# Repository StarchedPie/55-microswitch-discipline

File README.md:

# 55%
 55% keyboard using D2F microswitches, based on Coseyfannitutti's Discipline

[BOM, Build Guide, and Flashing Information](./doc)

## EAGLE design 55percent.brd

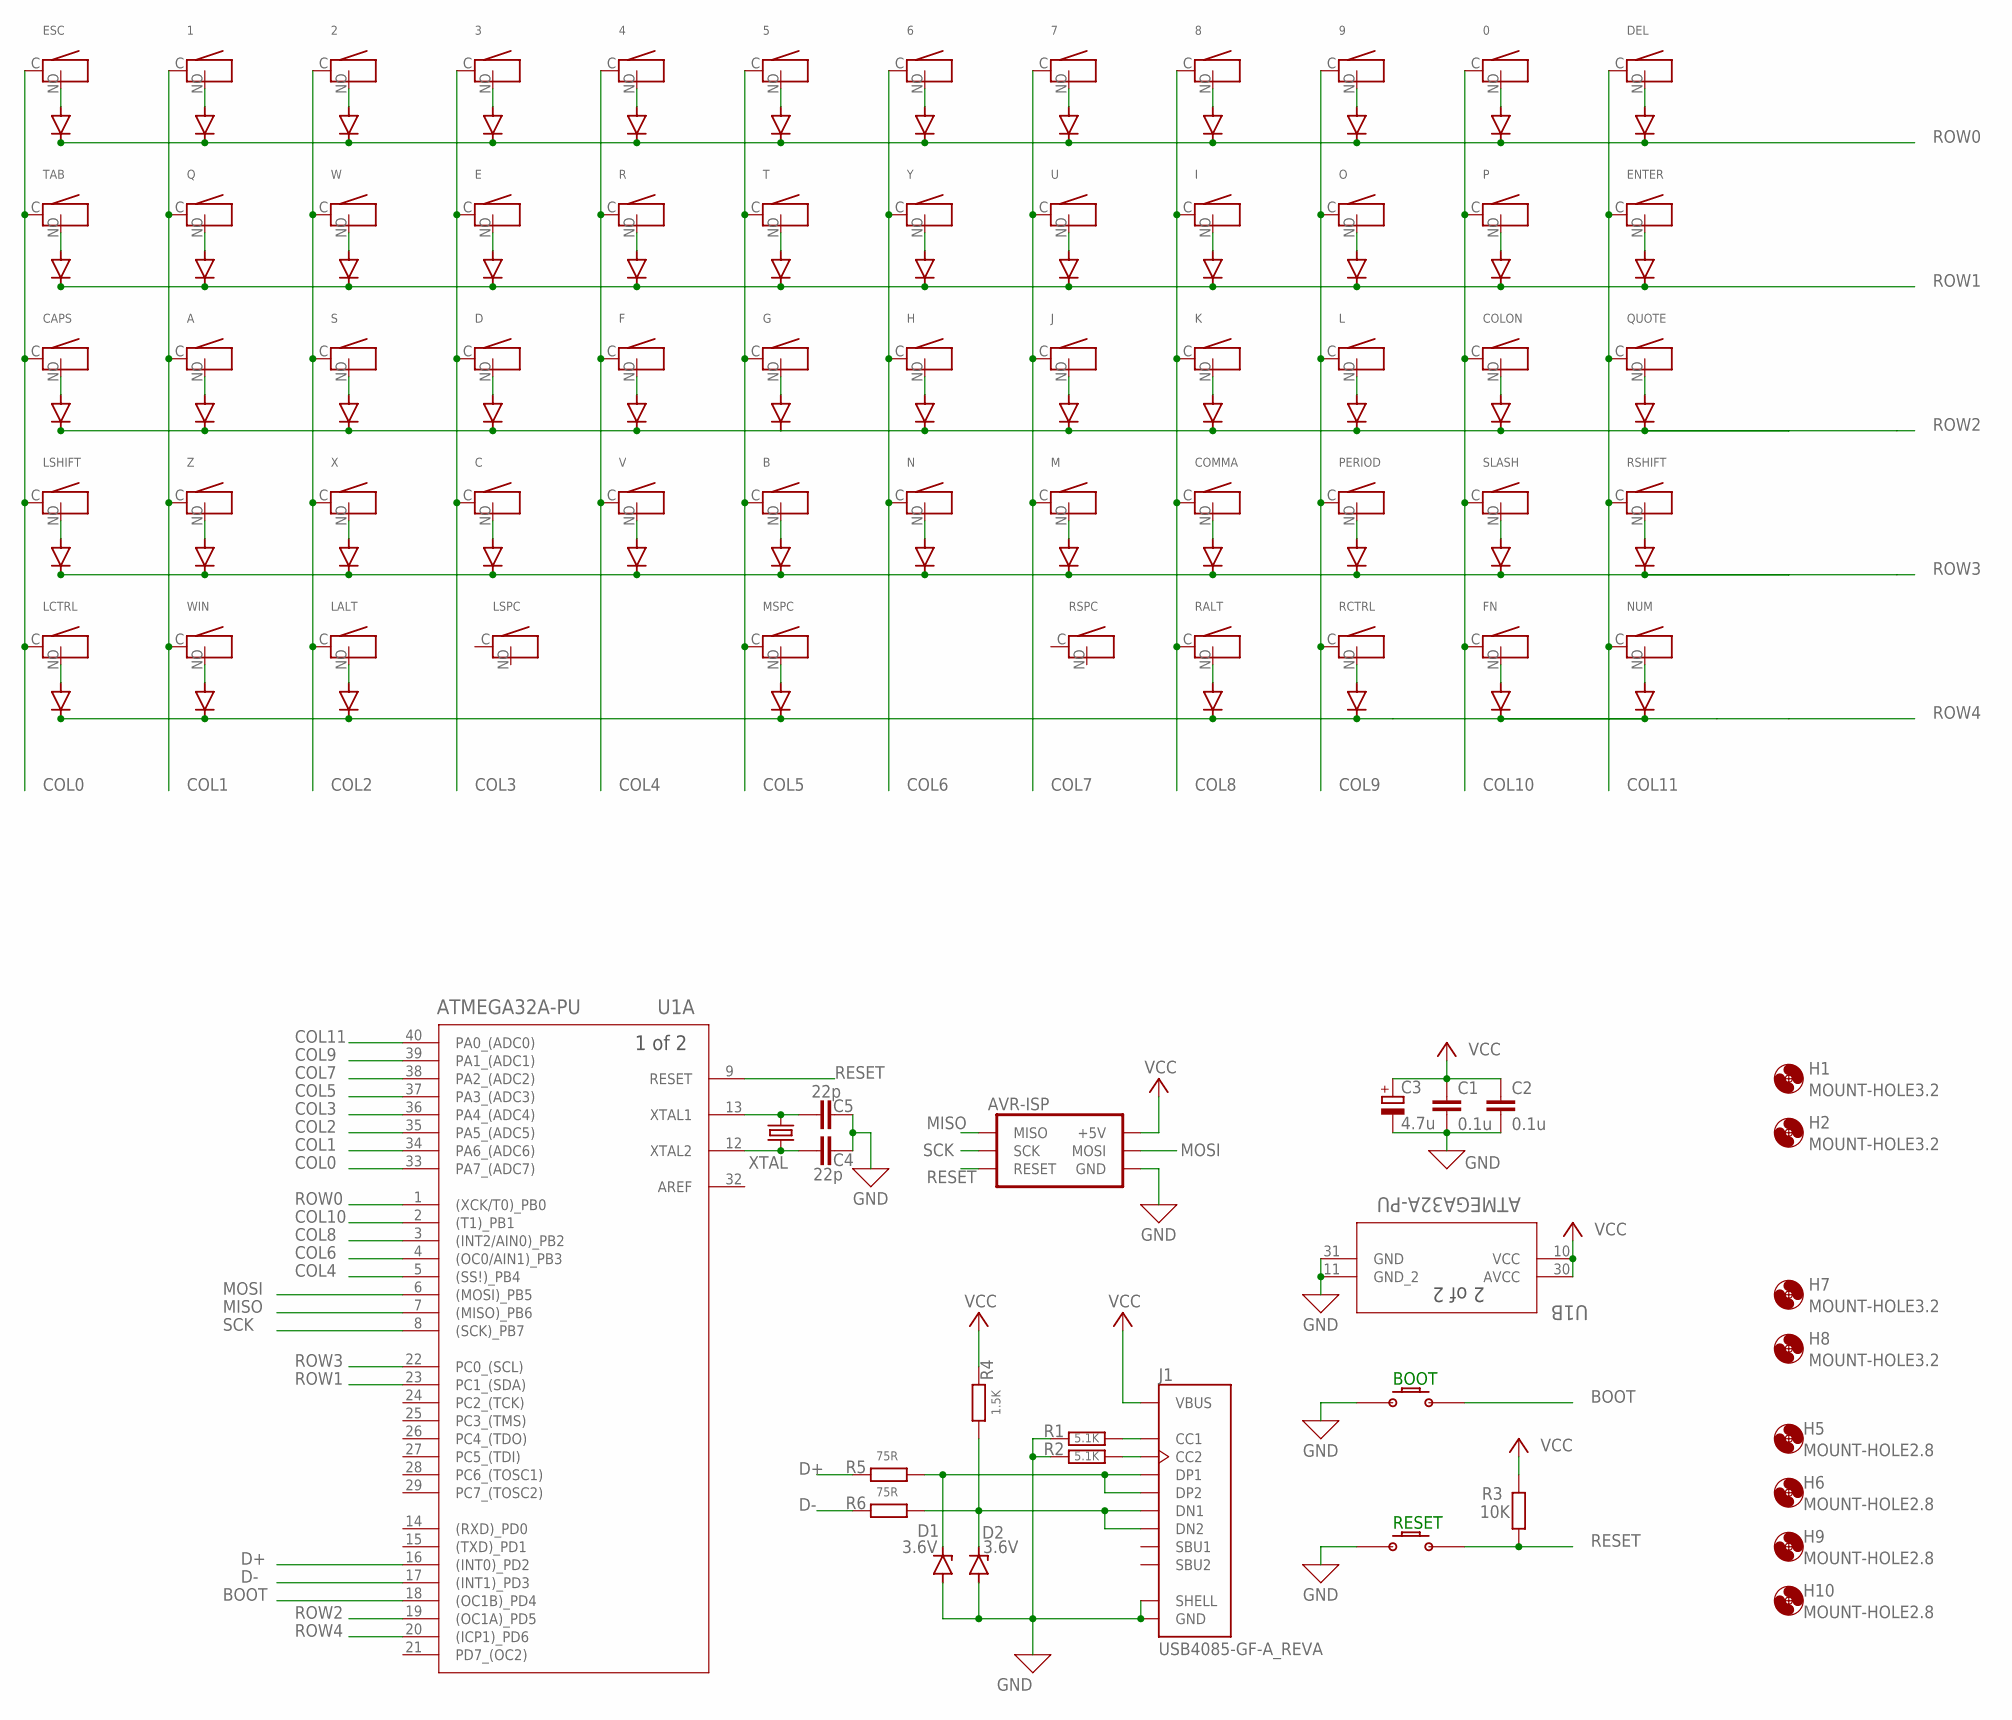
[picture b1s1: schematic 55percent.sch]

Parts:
0, 1, 2, 3, 4, 5, 6, 7, 8, 9: D2F_MICROSWITCH
A: D2F_MICROSWITCH
B: D2F_MICROSWITCH
C: D2F_MICROSWITCH
C1, C2: 0.1u; C025-024X044
C3: 4.7u; E2,5-5
C4, C5: 22p; C025-024X044
CAPS: D2F_MICROSWITCH
COLON: D2F_MICROSWITCH
COMMA: D2F_MICROSWITCH
D: D2F_MICROSWITCH
D1, D2: 3.6V; DO34Z7
D3, D4, D5, D6, D7, D8, D9, D10, D11, D12, D13, D14, D15, D16, D17, D18, D19, D20, D21, D23, D24, D25, D26, D28, D29, D30, D31, D32, D33, D34, D35, D36, D38, D39, D40, D41, D43, D44, D45, D46, D47, D48, D49, D50, D51, D52, D53, D54, D55, D56, D57, D58, D59, D60, D61, D62: 1N4004; DO41-10
DEL: D2F_MICROSWITCH
E: D2F_MICROSWITCH
ENTER: D2F_MICROSWITCH
ESC: D2F_MICROSWITCH
F: D2F_MICROSWITCH
FN: D2F_MICROSWITCH
G: D2F_MICROSWITCH
H: D2F_MICROSWITCH
H1, H2, H7, H8: MOUNT-HOLE3.2; 3,2
H5, H6, H9, H10: MOUNT-HOLE2.8; 2,2
I: D2F_MICROSWITCH
J: D2F_MICROSWITCH
J1: USB4085-GF-A_REVA; GCT_USB4085-GF-A_REVA
JP1: PINHD-2X3; 2X03
K: D2F_MICROSWITCH
L: D2F_MICROSWITCH
LALT: D2F_MICROSWITCH
LCTRL: D2F_MICROSWITCH
LSHIFT: D2F_MICROSWITCH
LSPC: D2F_MICROSWITCH
M: D2F_MICROSWITCH
MSPC: D2F_MICROSWITCH
N: D2F_MICROSWITCH
NUM: D2F_MICROSWITCH
O: D2F_MICROSWITCH
P: D2F_MICROSWITCH
PERIOD: D2F_MICROSWITCH
Q: D2F_MICROSWITCH
QUOTE: D2F_MICROSWITCH
R: D2F_MICROSWITCH
R1, R2: 5.1K; 0207/10
R3: 10K; 0207/10
R4: 1.5K; 0207/10
R5, R6: 75R; 0207/10
RALT: D2F_MICROSWITCH
RCTRL: D2F_MICROSWITCH
RSHIFT: D2F_MICROSWITCH
RSPC: D2F_MICROSWITCH
S: D2F_MICROSWITCH
SLASH: D2F_MICROSWITCH
T: D2F_MICROSWITCH
TAB: D2F_MICROSWITCH
U: D2F_MICROSWITCH
U1: ATMEGA32A-PU; 40P6
U$1, U$2: PTS636SK43LFS; PTS636SK43LFSTHT
V: D2F_MICROSWITCH
W: D2F_MICROSWITCH
WIN: D2F_MICROSWITCH
X: D2F_MICROSWITCH
XTAL: CRYSTALHC49S; HC49/S
Y: D2F_MICROSWITCH
Z: D2F_MICROSWITCH

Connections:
BOOT: U1.18 ((OC1B)_PD4), U$1.P$2
COL0: CAPS.C, ESC.C, LCTRL.C, LSHIFT.C, TAB.C, U1.33 (PA7_(ADC7))
COL1: 1.C, A.C, Q.C, U1.34 (PA6_(ADC6)), WIN.C, Z.C
COL2: 2.C, LALT.C, S.C, U1.35 (PA5_(ADC5)), W.C, X.C
COL3: 3.C, C.C, D.C, E.C, U1.36 (PA4_(ADC4))
COL4: 4.C, F.C, R.C, U1.5 ((SS!)_PB4), V.C
COL5: 5.C, B.C, G.C, MSPC.C, T.C, U1.37 (PA3_(ADC3))
COL6: 6.C, H.C, N.C, U1.4 ((OC0/AIN1)_PB3), Y.C
COL7: 7.C, J.C, M.C, U.C, U1.38 (PA2_(ADC2))
COL8: 8.C, COMMA.C, I.C, K.C, RALT.C, U1.3 ((INT2/AIN0)_PB2)
COL9: 9.C, L.C, O.C, PERIOD.C, RCTRL.C, U1.39 (PA1_(ADC1))
COL10: 0.C, COLON.C, FN.C, P.C, SLASH.C, U1.2 ((T1)_PB1)
COL11: DEL.C, ENTER.C, NUM.C, QUOTE.C, RSHIFT.C, U1.40 (PA0_(ADC0))
D+: R5.1, U1.16 ((INT0)_PD2)
D-: R6.1, U1.17 ((INT1)_PD3)
GND: C1.2, C2.2, C3.-, C4.1, C5.1, D1.A, D2.A, J1.A1 (GND), J1.A12 (GND), J1.B1 (GND), J1.B12 (GND), J1.P1 (SHELL), J1.P2 (SHELL), J1.P3 (SHELL), J1.P4 (SHELL), JP1.GND, R1.1, R2.1, U1.11 (GND_2), U1.31 (GND), U$1.P$1, U$2.P$1
MISO: JP1.MISO, U1.7 ((MISO)_PB6)
MOSI: JP1.MOSI, U1.6 ((MOSI)_PB5)
unnamed: J1.A5 (CC1), R1.2
unnamed: J1.B5 (CC2), R2.2
unnamed: D1.C, J1.A6 (DP1), J1.B6 (DP2), R5.2
unnamed: D7.A, LCTRL.NO (O)
unnamed: C5.2, U1.13 (XTAL1), XTAL.1
unnamed: C4.2, U1.12 (XTAL2), XTAL.2
unnamed: D2.C, J1.A7 (DN1), J1.B7 (DN2), R4.2, R6.2
unnamed: D6.A, LSHIFT.NO (O)
unnamed: CAPS.NO (O), D5.A
unnamed: D4.A, TAB.NO (O)
unnamed: D3.A, ESC.NO (O)
unnamed: D12.A, WIN.NO (O)
unnamed: D11.A, Z.NO (O)
unnamed: A.NO (O), D10.A
unnamed: D9.A, Q.NO (O)
unnamed: 1.NO (O), D8.A
unnamed: D17.A, LALT.NO (O)
unnamed: D16.A, X.NO (O)
unnamed: D15.A, S.NO (O)
unnamed: D14.A, W.NO (O)
unnamed: 2.NO (O), D13.A
unnamed: C.NO (O), D21.A
unnamed: D.NO (O), D20.A
unnamed: D19.A, E.NO (O)
unnamed: 3.NO (O), D18.A
unnamed: D26.A, V.NO (O)
unnamed: D25.A, F.NO (O)
unnamed: D24.A, R.NO (O)
unnamed: 4.NO (O), D23.A
unnamed: D32.A, MSPC.NO (O)
unnamed: B.NO (O), D31.A
unnamed: D30.A, G.NO (O)
unnamed: D29.A, T.NO (O)
unnamed: 5.NO (O), D28.A
unnamed: D36.A, N.NO (O)
unnamed: D35.A, H.NO (O)
unnamed: D34.A, Y.NO (O)
unnamed: 6.NO (O), D33.A
unnamed: D41.A, M.NO (O)
unnamed: D40.A, J.NO (O)
unnamed: D39.A, U.NO (O)
unnamed: 7.NO (O), D38.A
unnamed: D47.A, RALT.NO (O)
unnamed: COMMA.NO (O), D46.A
unnamed: D45.A, K.NO (O)
unnamed: D44.A, I.NO (O)
unnamed: 8.NO (O), D43.A
unnamed: D52.A, RCTRL.NO (O)
unnamed: D51.A, PERIOD.NO (O)
unnamed: D50.A, L.NO (O)
unnamed: D49.A, O.NO (O)
unnamed: 9.NO (O), D48.A
unnamed: D57.A, FN.NO (O)
unnamed: D56.A, SLASH.NO (O)
unnamed: COLON.NO (O), D55.A
unnamed: D54.A, P.NO (O)
unnamed: 0.NO (O), D53.A
unnamed: D62.A, NUM.NO (O)
unnamed: D61.A, RSHIFT.NO (O)
unnamed: D60.A, QUOTE.NO (O)
unnamed: D59.A, ENTER.NO (O)
unnamed: D58.A, DEL.NO (O)
RESET: JP1.RESET, R3.1, U1.9 (RESET), U$2.P$2
ROW0: D3.C, D8.C, D13.C, D18.C, D23.C, D28.C, D33.C, D38.C, D43.C, D48.C, D53.C, D58.C, U1.1 ((XCK/T0)_PB0)
ROW1: D4.C, D9.C, D14.C, D19.C, D24.C, D29.C, D34.C, D39.C, D44.C, D49.C, D54.C, D59.C, U1.23 (PC1_(SDA))
ROW2: D5.C, D10.C, D15.C, D20.C, D25.C, D30.C, D35.C, D40.C, D45.C, D50.C, D55.C, D60.C, U1.19 ((OC1A)_PD5)
ROW3: D6.C, D11.C, D16.C, D21.C, D26.C, D31.C, D36.C, D41.C, D46.C, D51.C, D56.C, D61.C, U1.22 (PC0_(SCL))
ROW4: D7.C, D12.C, D17.C, D32.C, D47.C, D52.C, D57.C, D62.C, U1.20 ((ICP1)_PD6)
SCK: JP1.SCK, U1.8 ((SCK)_PB7)
VCC: C1.1, C2.1, C3.+, J1.A4 (VBUS), J1.A9 (VBUS), J1.B4 (VBUS), J1.B9 (VBUS), JP1.+5V, R3.2, R4.1, U1.10 (VCC), U1.30 (AVCC)

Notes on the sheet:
BOOT
RESET

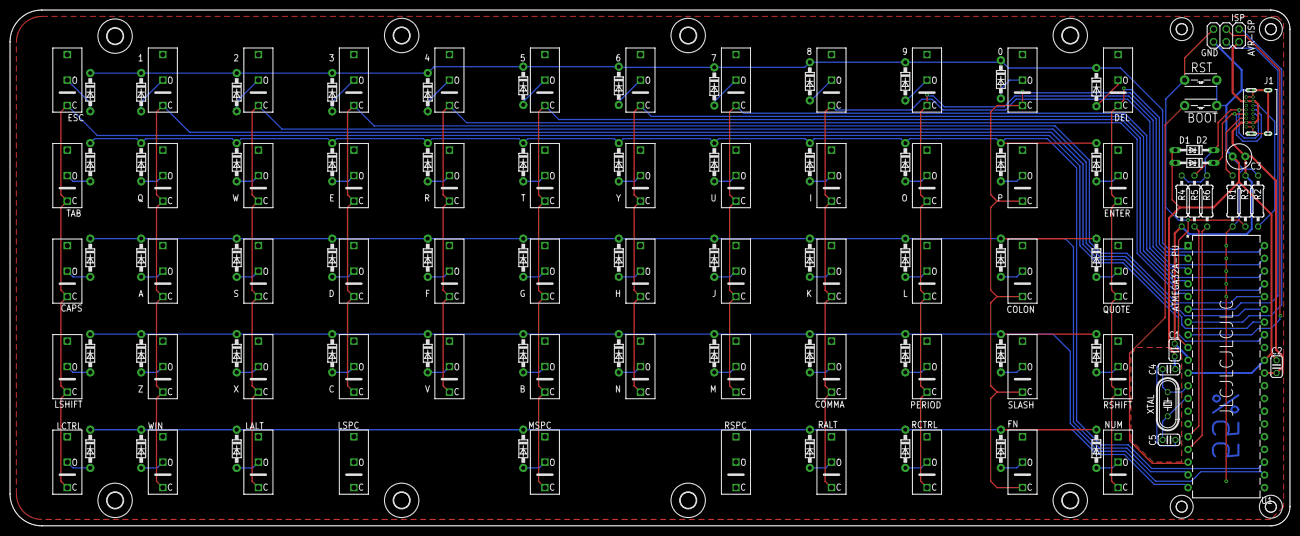
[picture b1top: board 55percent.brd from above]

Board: 2 copper layers, 255.3 x 102.9 mm, 145 parts (0 on the bottom side), 88 nets.

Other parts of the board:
H3, H4, H11, H12: MOUNT-HOLE3.2; 3,2

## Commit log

2020-04-17 Removed DISCIPLINE specific files, replaced with 55% files
2020-04-17 Keycap STL files added
2020-04-17 QMK firmware
2020-04-17 Create BOM
2020-04-17 Update BOM
2020-04-17 Put into 3rd person
2020-04-21 Fixed Resistor Placement
    If you have used a prior version of any of these files, contact me
2020-07-04 Debounce Modification
    Changed to use a new debounce algorithm which works much better with microswitches.
